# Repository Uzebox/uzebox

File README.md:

The Uzebox is an open source, retro-minimalist game console design. It is based on an AVR 8-bit general purpose microcontroller made by Atmel. The particularity of the system is that it's based on an interrupt driven engine and has no frame buffer. Functions such as video sync generation, tile rendering and music mixing is done realtime in software by a background task so games can easily be developed in C. The design goal was to be as simple as possible yet have good enough sound and graphics while leaving enough resources to implement interesting games. Emphasis was put on making it easy and fun to assemble and program for any hobbyists. The final design contains only two chips: an ATmega644 and an AD725 RGB-to-NTSC converter.

Many commercial versions were available: The Uzebox AVCore by Embedded Engineering llc and the Fuzebox by Adafruit Industries. There was also the Uzebox deluxe kit and the EUzebox, a version with a SCART interface.

Features:
* Interrupt driven: No cycle counting required, sound mixing and video generation are all made in the background
* 5 channels sound engine: The sound subsystem is composed of 3 wavetable channels, 1 noise and 1 PCM channel. Sound is 8-bit mono, mixed at ~15Khz
* 256 simultaneous colors arranged in a 3:3:2 color space (Red:3 bits, Green:3 bits, Blue: 2 bits)
* Resolution: 10+ video modes offering up to 360x224 pixels (tiles-only, tiles & sprites, and bitmap video modes)
* Full screen scrolling in certain video modes
* Sprites: 32+ simultaneous sprites
* Inputs supported: Two SNES compatible joypad inputs (including SNES mouse)
* MIDI IN: With a music sequencer, allows the creation of music directly on the console
* SD/MicroSD and FAT16/32 support
* 'Uzenet' extension for ESP8266 wifi and 128KB SPI RAM
* PS/2 keyboard interface
* Bootloader5 allows you to flash games from a standard FAT16/32 formatted SD card
* Cross-platform emulator with GDB support to ease development
* Multiple tools to convert MIDI, sound file and graphics to include files

The sources come complete with fully functional games, demos, content generation tools and even a cross-platform emulator!

**To find out more, please check out the project's sites:**
* [Getting started](https://uzebox.org/wiki/Getting_Started_on_the_Uzebox): How to install the toolchains, IDEs and build the codebase. Then move on to tutorials and the rest of the documentation.  
* [Main website](https://uzebox.org): The main hub with news, links, downloads and more.
* [Wiki](https://uzebox.org/wiki): All the project's documentation.
* [Forums](https://uzebox.org/forums): Share your new game and discuss everything Uzebox.

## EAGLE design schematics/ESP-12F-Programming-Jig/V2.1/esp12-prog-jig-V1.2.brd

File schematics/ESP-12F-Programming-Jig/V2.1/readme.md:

# ESP-12E/F Programming Jig V1.2 

A jig to program the ESP-12E/F modules based on Espressif's ESP8266 Wi-fi module. Specficially made for FTDI TTL-232R cables.

### Features
* Dual voltage support for the TTL-232R-3V3 (3.3V I/O) and TTL-232R-5V (5V I/O) cables
* Can use pogo pins or headers as mating options
* Programming switches
* Most discretes parts can be ommited if only 3.3V is to be supported

### Notes
* See the the [Uzebox WIKI](https://uzebox.org/wiki/ESP8266_Manual_Upgrade) on the software and procedure required to upgrade the ESP8266 firmware.
* A 3D printed enclosure is available [here](https://github.com/Uzebox/uzebox/tree/master/cad/Enclosures/ESP-12F-Programming-Jig/V1.2).
* Schematic and PCB design files are provided in EAGLE format (.sch, .brd)
* The provided Gerber files can simply be zipped toghether and directly uploaded to PCB manufacturer such as [JLCPCB](https://jlcpcb.com/) and [PCBWay](https://www.pcbway.com/).

### Revisions 
#### V1.2 - Feb-2023
* Replaced tactile switches with through hole versions
* Added color legend on how to connect the FTDI cable correctly

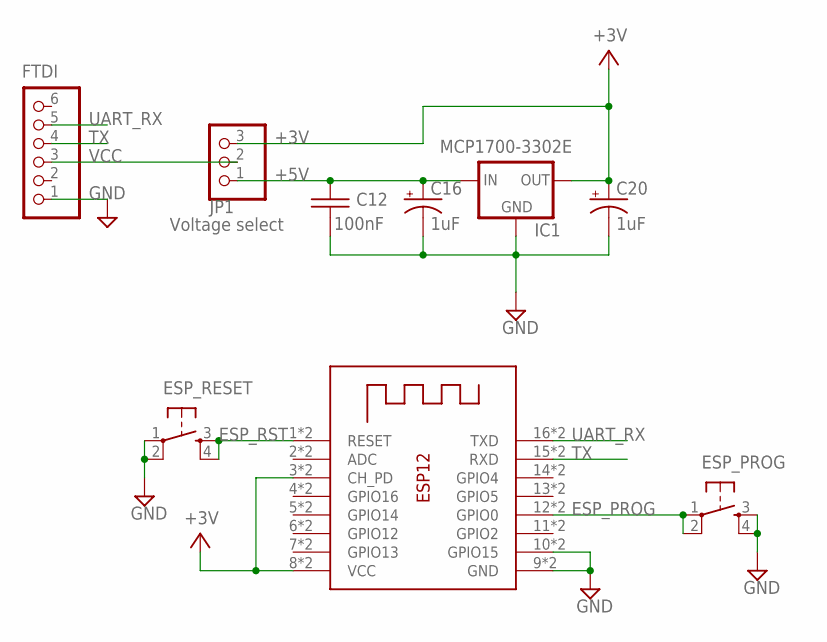
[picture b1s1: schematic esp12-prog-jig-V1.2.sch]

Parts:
C12: 100nF; UZEBOX_CAP_C025
C16, C20: 1uF; UZEBOX_CAP_E5X6
ESP_PROG: UZEBOX_TACTILE_SWITCHPTH; TACTILE-PTH
ESP_RESET: UZEBOX_TACTILE_SWITCHPTH; TACTILE-PTH
FTDI: PINHD-1X6/90; 1X06/90
IC1: MCP1700-3302E; ADAFRUIT_TO92-INLINE
JP1: Voltage select; 1X03
X1: ESP8266-12F; UZEBOX_ESP-12_TH

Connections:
+3V: C20.+, IC1.3 (OUT), JP1.3, X1.3 (CH_PD), X1.8 (VCC), X1.P$3 (CH_PD), X1.P$8 (VCC)
+5V: C12.1, C16.+, IC1.2 (IN), JP1.1
ESP_PROG: ESP_PROG.1, ESP_PROG.2, X1.12 (GPIO0), X1.P$12 (GPIO0)
ESP_RST: ESP_RESET.3, ESP_RESET.4, X1.1 (RESET), X1.P$1 (RESET)
GND: C12.2, C16.-, C20.-, ESP_PROG.3, ESP_PROG.4, ESP_RESET.1, ESP_RESET.2, FTDI.1, IC1.1 (GND), X1.9 (GND), X1.10 (GPIO15), X1.P$9 (GND), X1.P$10 (GPIO15)
TX: FTDI.4, X1.15 (RXD), X1.P$15 (RXD)
UART_RX: FTDI.5, X1.16 (TXD), X1.P$16 (TXD)
VCC: FTDI.3, JP1.2

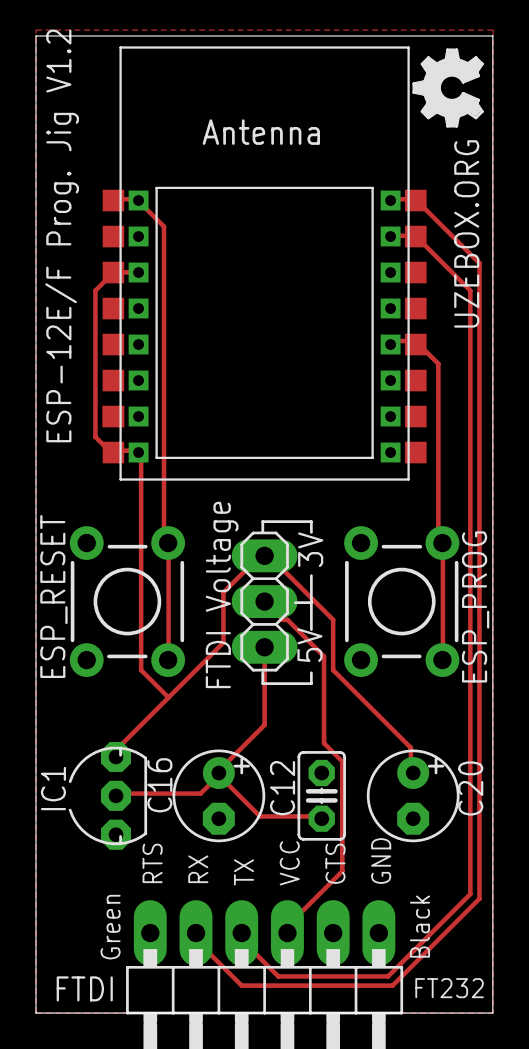
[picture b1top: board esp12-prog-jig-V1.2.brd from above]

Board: 2 copper layers, 25.4 x 54.3 mm, 10 parts (0 on the bottom side), 8 nets.

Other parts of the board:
U$1: OSHW_FILLX150_NOTEXT

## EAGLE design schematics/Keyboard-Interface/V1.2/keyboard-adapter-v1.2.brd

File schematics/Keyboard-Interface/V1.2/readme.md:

# Uzebox Keyboard Interface V1.2 

The keyboard interface allows the Uzebox to communicate with a standard PS/2 keyboard.

See https://uzebox.org/wiki/Uzebox_Keyboard_Interface for more details on the implementation of the interface and the assembly guide.
### Features
* Based on the Atmel ATtiny85/45/25 8-pin DIP
* PS/2 Interface to keyboard 
* Communicates with the Uzebox via a controller port
* Supports bi-directionnal communication
* ISP port to allow reprogramming of the firmware
* Implements the Uzebus protocol

### Notes
* keyboard-adapter-firmware-v2.hex is the latest firmware to be flashed on the ATtiny85. The firmware is built by the [KeyboardFirmware project](/demos/KeyboardFirmware).
* Schematic and PCB design files are provided in EAGLE format (.sch, .brd)
* The provided Gerber files can simply be zipped toghether and directly uploaded to PCB manufacturer such as [JLCPCB](https://jlcpcb.com/) and [PCBWay](https://www.pcbway.com/).

### Revisions 
#### V1.2 - Feb-2023
* Corrected layout issue: Ajusted PCB layout so the ISP progammer's 6 pins header could fit.
* Added pullups on the PS/2 lines since the internal AVR pullups would not work when the tiny85 wanted to send commands to the keyboard.
* Added series resistors on the SNES lines to avoid interfering with ISP programming. Added for development and firmware updates.
* Revamped the PCB design and labeled all components
* Support sending host commands to the keyboard. Implemented to support keyboard that requires the host to send any command right after a reset/BAT. Otherwise the keyboard re-enters BAT (self-test) endlessly sending 0xAA on the bus. This allows the support of PS/2 Perixx keyboards.

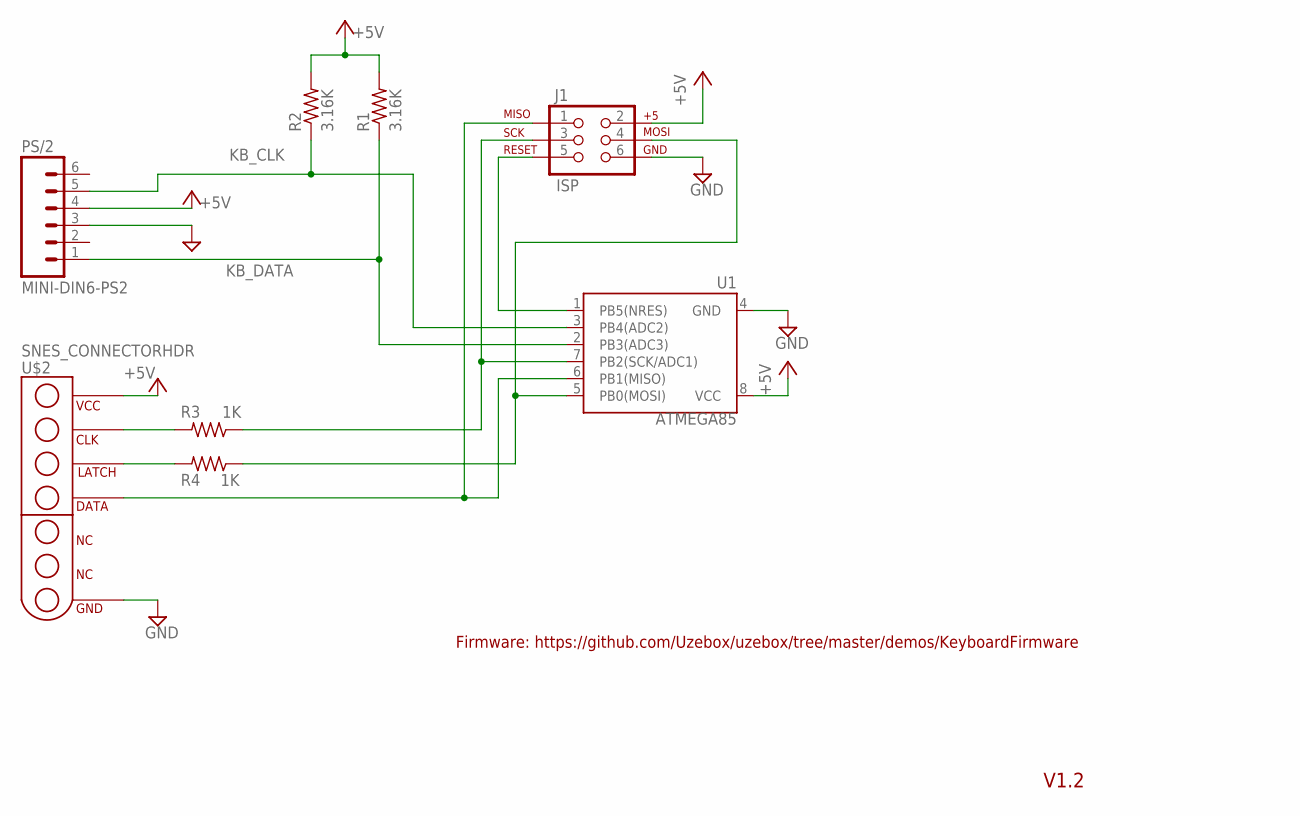
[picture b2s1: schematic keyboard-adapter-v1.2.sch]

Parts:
ATMEGA85: U1; DIP762W53P254L927H508Q8B
J1: ISP; 2X3
PS/2: MINI-DIN6-PS2; MINI-DIN6
R1, R2: 3.16K; 0207/10
R3, R4: 1K; 0207/10
U$2: SNES_CONNECTORHDR; SNES_CONN-HDR5

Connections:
+5V: ATMEGA85.8 (VCC), J1.2, PS/2.4, R1.2, R2.2, U$2.P$5 (VCC)
GND: ATMEGA85.4 (GND), J1.6, PS/2.3, U$2.P$1 (GND)
KB_CLK: ATMEGA85.3 (PB4(ADC2)), PS/2.5, R2.1
KB_DATA: ATMEGA85.2 (PB3(ADC3)), PS/2.1, R1.1
MISO: ATMEGA85.6 (PB1(MISO)), J1.1, U$2.P$2 (DATA)
MOSI: ATMEGA85.5 (PB0(MOSI)), J1.4, R4.1
RESET: ATMEGA85.1 (PB5(NRES)), J1.5
SCK: ATMEGA85.7 (PB2(SCK/ADC1)), J1.3, R3.1
S_CLK: R3.2, U$2.P$4 (CLK)
S_LATCH: R4.2, U$2.P$3 (LATCH)

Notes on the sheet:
V1.2
Firmware: https://github.com/Uzebox/uzebox/tree/master/demos/KeyboardFirmware

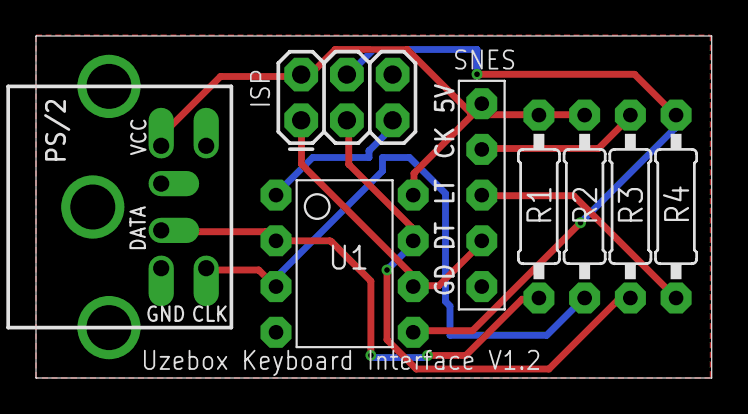
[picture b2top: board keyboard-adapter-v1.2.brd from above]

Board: 2 copper layers, 37.5 x 19.0 mm, 9 parts (1 on the bottom side), 10 nets.

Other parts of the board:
U$1: OSHW_FILLX150_NOTEXT

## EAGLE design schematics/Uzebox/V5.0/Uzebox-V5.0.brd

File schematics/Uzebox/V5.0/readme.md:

### Schematic and PCB design files for the Uzebox reference design V5.0

The Uzebox is a retro-minimalist 8-bit video game console based on only 2 chips.
### Features
* Atmel ATMega644/A/P/PA overclocked at 28Mhz
* NTSC video generation with the AD725 RGB-to-NTSC converter chip
* Composite and S-Video outputs
* SD card interface
* ESP-12E/F Wi-fi module that can be soldered via castlated pads or in a through hole fashion.
* SPI RAM support
* Two SNES controller sockets
* Reset and soft power buttons
* ISP Port
* Extension header

### Revisions
* PCB rev.1.3.3
* Replaced the MIDI interface with Uzenet interface
* Added second ISP footprint for 90 deg connectors
* New footprint for SD card connector (see BOM)

### Assembly guide
* The assembly guide is part of the project [here](Uzebox-V5.0-assembly-guide.md).

### Notes
* Schematic and PCB design files are provided in EAGLE format (.sch, .brd)
* The provided Gerber files can simply be zipped toghether and directly uploaded to PCB manufacturer such as [JLCPCB](https://jlcpcb.com/) and [PCBWay](https://www.pcbway.com/).
* A Digikey shopping list is available to quickly order all parts. The list is continuously maintained as parts goes out of stock. https://www.digikey.ca/en/mylists/list/QP8GNGSW4R

### Links
* [Uzebox website](https://uzebox.org/index.php)
* [Uzebox Forums](https://uzebox.org/forums/)
* [uzebox WIKI](https://uzebox.org/wiki/Main_Page)

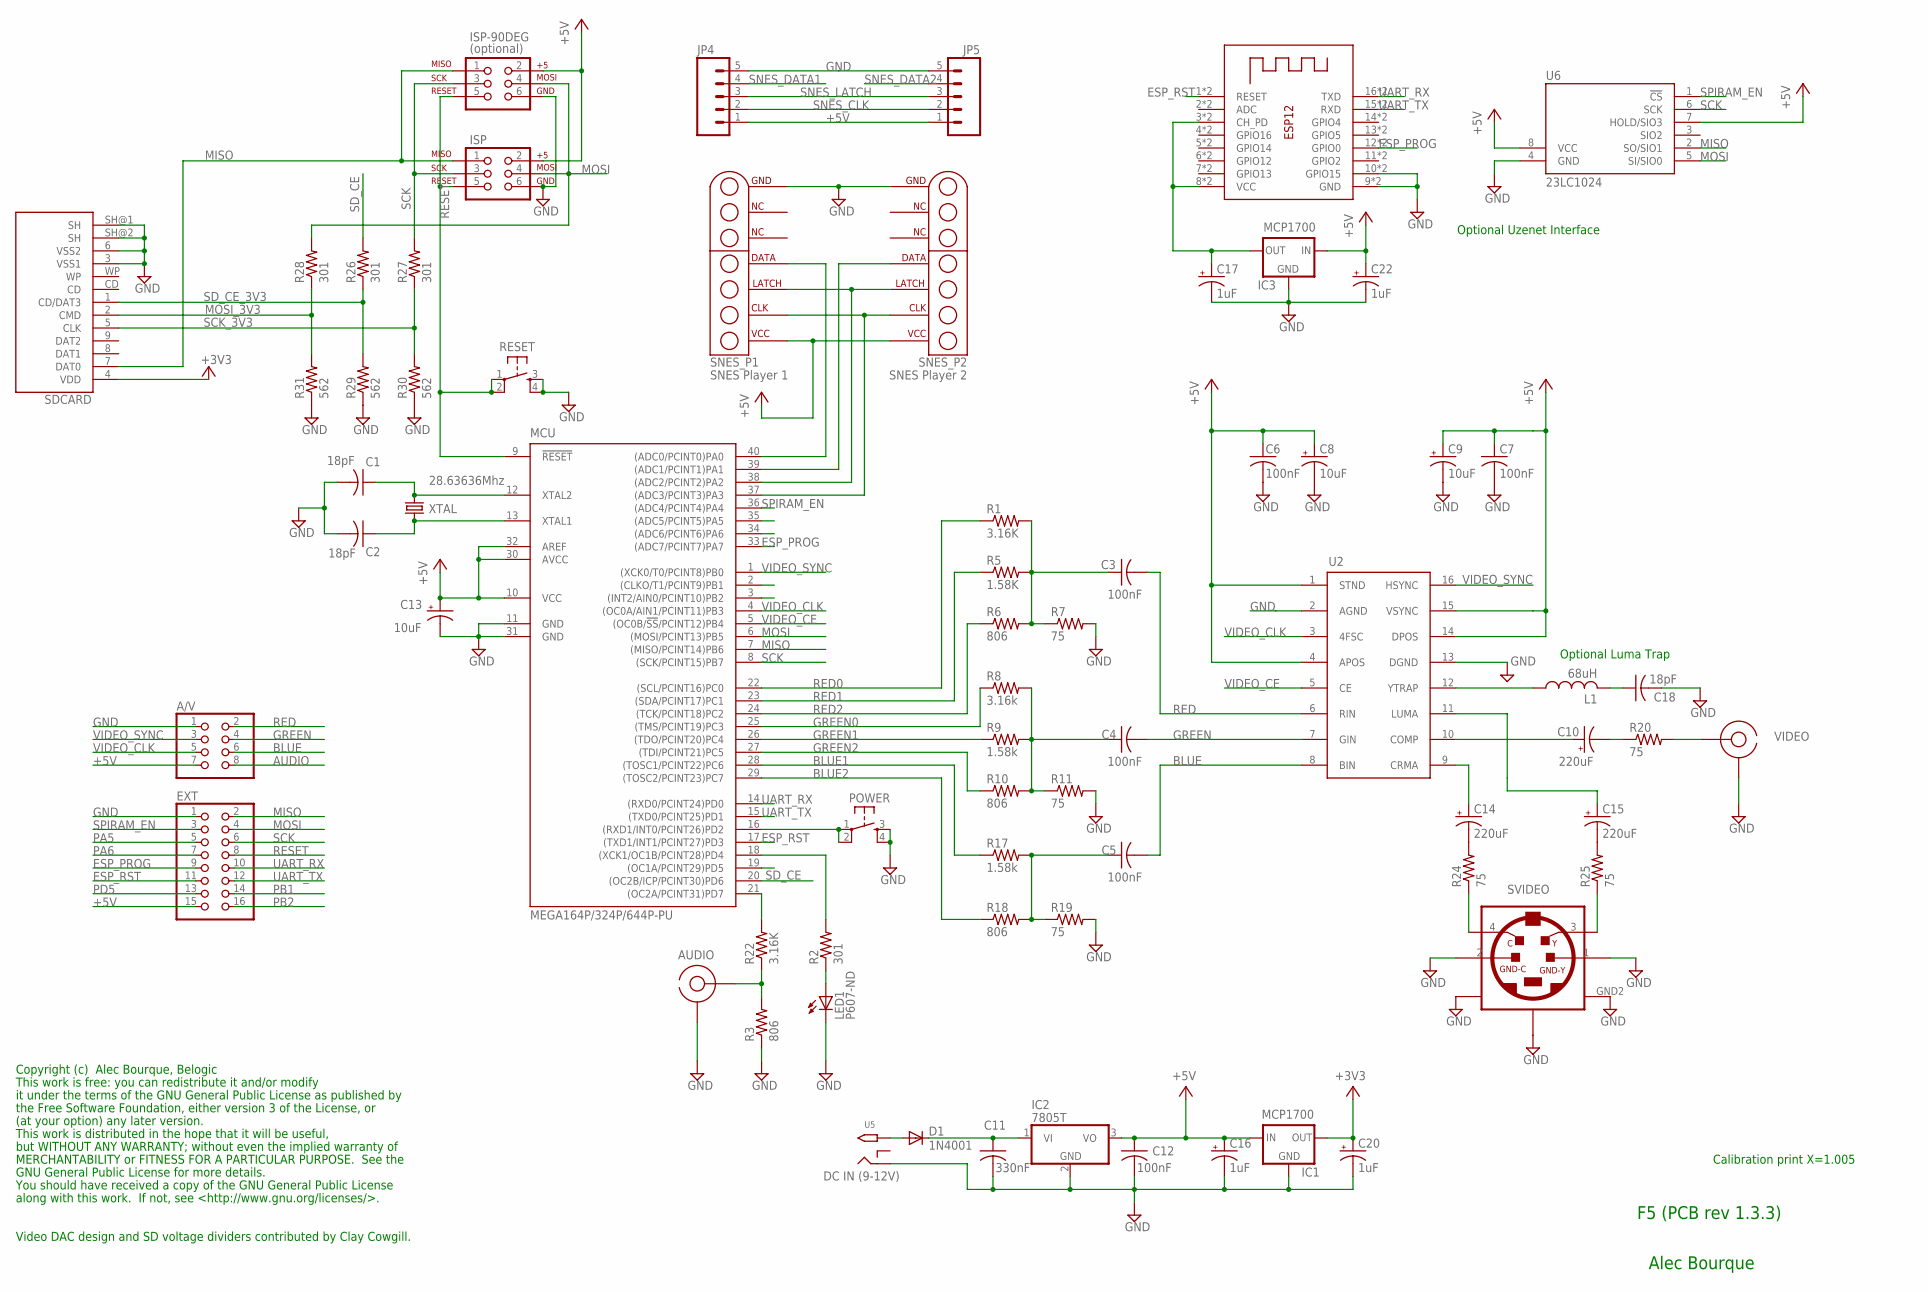
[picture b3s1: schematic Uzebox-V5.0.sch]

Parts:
A/V: PINHD-2X4; 2X04
AD725: AD725; SO16W
AUDIO: RCA
C1, C2, C18: 18pF; C025-025X050
C3, C4, C5, C6, C7, C12: 100nF; C025-025X050
C8, C9, C13: 10uF; E2,5-6
C10, C14, C15: 220uF; E2,5-6
C11: 330nF; C025-025X050
C16, C20: 1uF; E2,5-6
C17, C22: 1uF; E2-4
D1: 1N4001; DO41-10
ESP-12: ESP-12; UZEBOX_ESP-12_TH
EXT: PINHD-2X8; 2X08
IC1, IC3: MCP1700; TO92-INLINE
IC2: 7805T; TO220H
ISP: AVR_SPI_PRG_6PTH; 2X3
ISP-90DEG: (optional); 2X3
JP4, JP5: M05PTH; 1X05
L1: 68uH; 6000-XXXX-RC
LED1: P607-ND; LED3MM
MCU: MEGA164P/324P/644P-PU; DIL40
POWER: USER; TACTILE-PTH
R1, R22: 3.16K; 0207/10
R2, R26, R27, R28: 301; 0207/10
R3, R6, R10, R18: 806; 0207/10
R5: 1.58K; 0207/10
R7, R11, R19, R20, R24, R25: 75; 0207/10
R8: 3.16k; 0207/10
R9, R17: 1.58k; 0207/10
R29, R30, R31: 562; 0207/10
RESET: RESET; TACTILE-PTH
SDCARD: SD_CARD_SOCKET4UCON; SDCARD_4UCONN
SNES_P1: SNES Player 1; SNES_CONNECTOR
SNES_P2: SNES Player 2; SNES_CONNECTOR
SVIDEO: S-VIDEO OUT; MINIDIN4
U5: DC IN; PJ-102A
U6: 23LC1024; DIL08
VIDEO: RCA
XTAL: 28.63636Mhz; HC49/S

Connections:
3V3_ESP: C17.+, ESP-12.3 (CH_PD), ESP-12.8 (VCC), ESP-12.P$3 (CH_PD), ESP-12.P$8 (VCC), IC3.3 (OUT)
+3V3: C20.+, IC1.3 (OUT), SDCARD.4 (VDD)
+5V: A/V.7, AD725.1 (STND), AD725.4 (APOS), AD725.14 (DPOS), AD725.15 (VSYNC), C6.1, C7.1, C8.+, C9.+, C12.1, C13.+, C16.+, C22.+, EXT.15, IC1.2 (IN), IC2.3 (VO), IC3.2 (IN), ISP.2, ISP-90DEG.2, JP4.1, JP5.1, MCU.10 (VCC), MCU.30 (AVCC), MCU.32 (AREF), SNES_P1.P$8 (VCC), SNES_P2.P$8 (VCC), U6.7 (HOLD/SIO3), U6.8 (VCC)
AUDIO: A/V.8, AUDIO.SIG, R3.2, R22.1
BLUE: A/V.6, AD725.8 (BIN), C5.2
BLUE1: MCU.28 ((TOSC1/PCINT22)PC6), R17.1
BLUE2: MCU.29 ((TOSC2/PCINT23)PC7), R18.1
ESP_PROG: ESP-12.12 (GPIO0), ESP-12.P$12 (GPIO0), EXT.9, MCU.33 ((ADC7/PCINT7)PA7)
ESP_RST: ESP-12.1 (RESET), ESP-12.P$1 (RESET), EXT.11, MCU.17 ((TXD1/INT1/PCINT27)PD3)
GND: A/V.1, AD725.2 (AGND), AD725.13 (DGND), AUDIO.GND, C1.2, C2.2, C6.2, C7.2, C8.-, C9.-, C11.2, C12.2, C13.-, C16.-, C17.-, C18.2, C20.-, C22.-, ESP-12.9 (GND), ESP-12.10 (GPIO15), ESP-12.P$9 (GND), ESP-12.P$10 (GPIO15), EXT.1, IC1.1 (GND), IC2.2 (GND), IC3.1 (GND), ISP.6, ISP-90DEG.6, JP4.5, JP5.5, LED1.K (C), MCU.11 (GND), MCU.31 (GND), POWER.3, POWER.4, R3.1, R7.2, R11.2, R19.2, R29.1, R30.1, R31.1, RESET.3, RESET.4, SDCARD.3 (VSS1), SDCARD.6 (VSS2), SDCARD.SH@1 (SH), SDCARD.SH@2 (SH), SNES_P1.P$14 (GND), SNES_P2.P$14 (GND), SVIDEO.1 (GND-Y), SVIDEO.2 (GND-C), SVIDEO.GND1, SVIDEO.GND2, SVIDEO.GND3, U5.RING, U6.4 (GND), VIDEO.GND
GREEN: A/V.4, AD725.7 (GIN), C4.2
GREEN0: MCU.25 ((TMS/PCINT19)PC3), R8.1
GREEN1: MCU.26 ((TDO/PCINT20)PC4), R9.1
GREEN2: MCU.27 ((TDI/PCINT21)PC5), R10.1
MISO: EXT.2, ISP.1, ISP-90DEG.1, MCU.7 ((MISO/PCINT14)PB6), SDCARD.7 (DAT0), U6.2 (SO/SIO1)
MOSI: EXT.4, ISP.4, ISP-90DEG.4, MCU.6 ((MOSI/PCINT13)PB5), R28.2, U6.5 (SI/SIO0)
MOSI_3V3: R28.1, R31.2, SDCARD.2 (CMD)
unnamed: AD725.12 (YTRAP), L1.1
unnamed: C18.1, L1.2
unnamed: C5.1, R17.2, R18.2, R19.1
unnamed: C4.1, R8.2, R9.2, R10.2, R11.1
unnamed: C3.1, R1.2, R5.2, R6.2, R7.1
unnamed: C10.-, R20.1
unnamed: AD725.10 (COMP), C10.+
unnamed: R20.2, VIDEO.SIG
unnamed: C1.1, MCU.12 (XTAL2), XTAL.2
unnamed: D1.A, U5.TIP
unnamed: C14.-, R24.2
unnamed: C2.1, MCU.13 (XTAL1), XTAL.1
unnamed: MCU.21 ((OC2A/PCINT31)PD7), R22.2
unnamed: C11.1, D1.C, IC2.1 (VI)
unnamed: MCU.18 ((XCK1/OC1B/PCINT28)PD4), R2.2
unnamed: LED1.A, R2.1
unnamed: C15.-, R25.2
unnamed: AD725.11 (LUMA), C15.+
unnamed: AD725.9 (CRMA), C14.+
unnamed: R24.1, SVIDEO.4 (C)
unnamed: R25.1, SVIDEO.3 (Y)
PA5: EXT.5, MCU.35 ((ADC5/PCINT5)PA5)
PA6: EXT.7, MCU.34 ((ADC6/PCINT6)PA6)
PB1: EXT.14, MCU.2 ((CLKO/T1/PCINT9)PB1)
PB2: EXT.16, MCU.3 ((INT2/AIN0/PCINT10)PB2)
PD5: EXT.13, MCU.19 ((OC1A/PCINT29)PD5)
POWER_SW: MCU.16 ((RXD1/INT0/PCINT26)PD2), POWER.1, POWER.2
RED: A/V.2, AD725.6 (RIN), C3.2
RED0: MCU.22 ((SCL/PCINT16)PC0), R1.1
RED1: MCU.23 ((SDA/PCINT17)PC1), R5.1
RED2: MCU.24 ((TCK/PCINT18)PC2), R6.1
RESET: EXT.8, ISP.5, ISP-90DEG.5, MCU.9 (!RESET), RESET.1, RESET.2
SCK: EXT.6, ISP.3, ISP-90DEG.3, MCU.8 ((SCK/PCINT15)PB7), R27.2, U6.6 (SCK)
SCK_3V3: R27.1, R30.2, SDCARD.5 (CLK)
SD_CE: MCU.20 ((OC2B/ICP/PCINT30)PD6), R26.2
SD_CE_3V3: R26.1, R29.2, SDCARD.1 (CD/DAT3)
SNES_CLK: JP4.2, JP5.2, MCU.37 ((ADC3/PCINT3)PA3), SNES_P1.P$9 (CLK), SNES_P2.P$9 (CLK)
SNES_DATA1: JP4.4, MCU.40 ((ADC0/PCINT0)PA0), SNES_P1.P$11 (DATA)
SNES_DATA2: JP5.4, MCU.39 ((ADC1/PCINT1)PA1), SNES_P2.P$11 (DATA)
SNES_LATCH: JP4.3, JP5.3, MCU.38 ((ADC2/PCINT2)PA2), SNES_P1.P$10 (LATCH), SNES_P2.P$10 (LATCH)
SPIRAM_EN: EXT.3, MCU.36 ((ADC4/PCINT4)PA4), U6.1 (!CS)
UART_RX: ESP-12.16 (TXD), ESP-12.P$16 (TXD), EXT.10, MCU.14 ((RXD0/PCINT24)PD0)
UART_TX: ESP-12.15 (RXD), ESP-12.P$15 (RXD), EXT.12, MCU.15 ((TXD0/PCINT25)PD1)
VIDEO_CE: AD725.5 (CE), MCU.5 ((OC0B/!SS!/PCINT12)PB4)
VIDEO_CLK: A/V.5, AD725.3 (4FSC), MCU.4 ((OC0A/AIN1/PCINT11)PB3)
VIDEO_SYNC: A/V.3, AD725.16 (HSYNC), MCU.1 ((XCK0/T0/PCINT8)PB0)

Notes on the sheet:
Optional Luma Trap
Alec Bourque
Copyright (c) Alec Bourque, Belogic
This work is free: you can redistribute it and/or modify
it under the terms of the GNU General Public License as published by
the Free Software Foundation, either version 3 of the License, or
(at your option) any later version.
This work is distributed in the hope that it will be useful,
but WITHOUT ANY WARRANTY; without even the implied warranty of
MERCHANTABILITY or FITNESS FOR A PARTICULAR PURPOSE. See the
GNU General Public License for more details.
You should have received a copy of the GNU General Public License
along with this work. If not, see <http://www.gnu.org/licenses/>.
Calibration print X=1.005
Video DAC design and SD voltage dividers contributed by Clay Cowgill.
F5 (PCB rev 1.3.3)
Optional Uzenet Interface

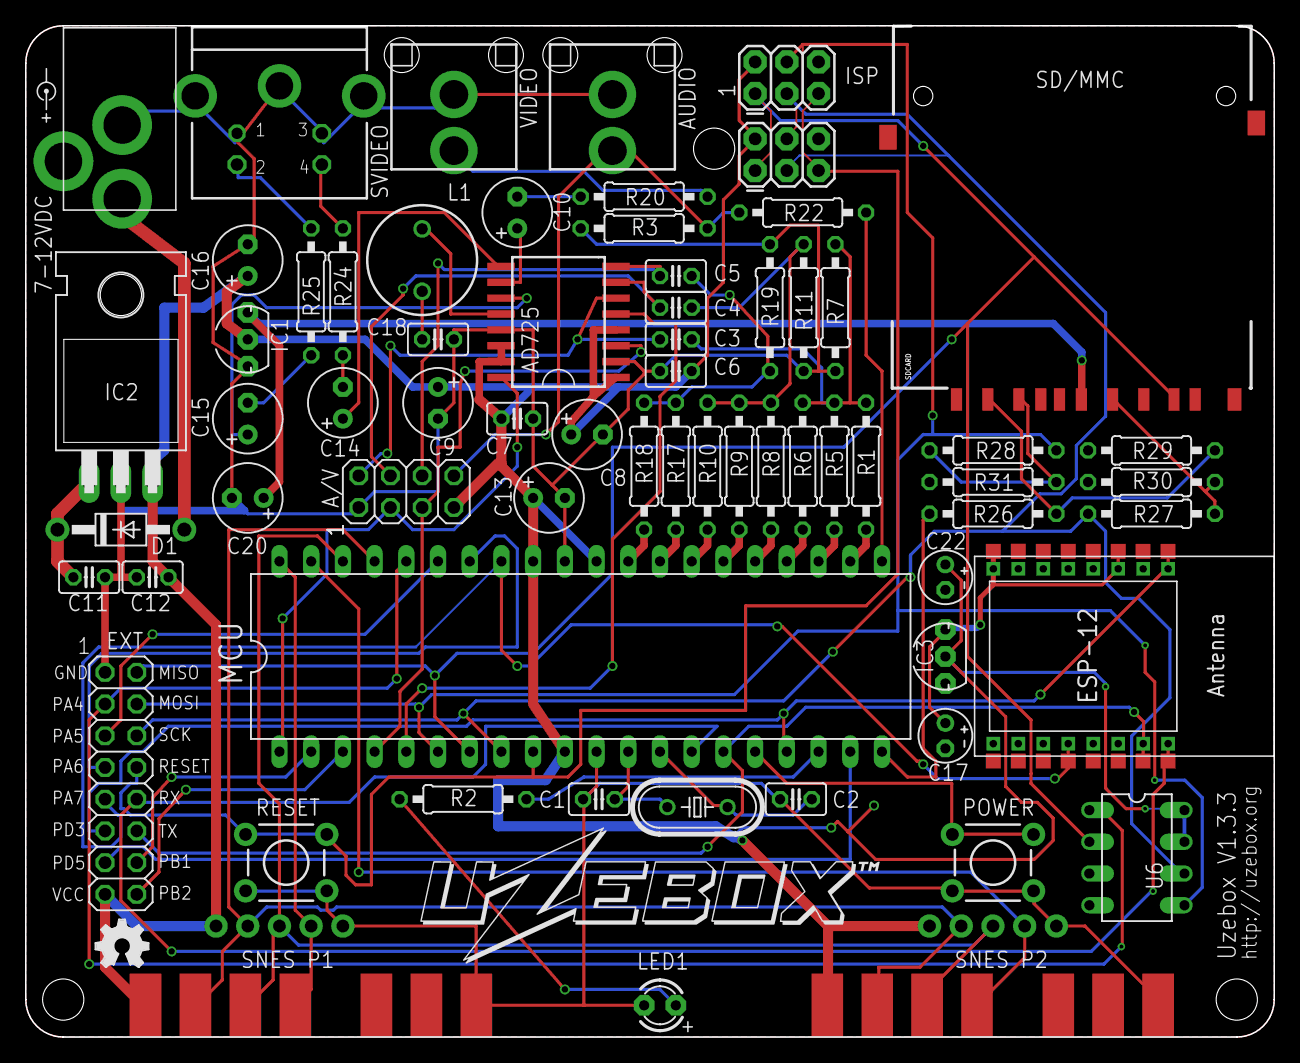
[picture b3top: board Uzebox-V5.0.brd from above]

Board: 2 copper layers, 100.0 x 81.0 mm, 79 parts (0 on the bottom side), 63 nets.

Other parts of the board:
U$1: OSHW_FILLX150_NOTEXT
U$2, U$3, U$4: STAND-OFF
U$6: LOGO
U$7: POWER
U$8, U$9, U$10, U$11: BUMPON

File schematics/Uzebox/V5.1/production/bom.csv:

Designator,Footprint,Quantity,Value,LCSC Part #
A/V,2X04,1,PINHD-2X4,
AD725,SO16W,1,AD725,
"AUDIO, VIDEO",RCA,2,RCA,
"C1, C18, C2",C025-025X050,3,18pF,
"C10, C14, C15","E2,5-6",3,220uF,
C11,C025-025X050,1,330nF,
"C12, C3, C4, C5, C6, C7",C025-025X050,6,100nF,
"C13, C8, C9","E2,5-6",3,10uF,
"C16, C20","E2,5-6",2,1uF,
"C17, C22",E2-4,2,1uF,
D1,DO41-10,1,1N4001,
D2,DO35-7,1,BAT85,
ESP-12,UZEBOX_ESP-12_TH,1,ESP-12,
EXT,2X08,1,PINHD-2X8,
"IC1, IC3",TO92-INLINE,2,MCP1700,
IC2,TO220H,1,78T05,
ISP,2X3,1,AVR_SPI_PRG_6PTH,
ISP-90DEG1,2X3,1,(optional),
J1,PinHeader_1x05_P2.54mm_Vertical,1,P1,
J2,PinHeader_1x05_P2.54mm_Vertical,1,P2,
L1,6000-XXXX-RC,1,68uH,
LED,LED3MM,1,P607-ND,
MCU,DIL40,1,ATMEGA644P-PU,
POWER,TACTILE-PTH,1,USER,
"R1, R12, R13, R22, R4, R8",0207_10,6,3.16K,
"R10, R18, R3, R6",0207_10,4,806,
"R11, R19, R20, R24, R25, R7",0207_10,6,75,
"R17, R5, R9",0207_10,3,1.58k,
"R2, R27, R28",0207_10,3,301,
"R30, R31",0207_10,2,562,
RESET,TACTILE-PTH,1,RESET,
SDCARD,SDCARD_4UCONN,1,SD_CARD_SOCKET4UCON,
SNES_P1,SNES_CONNECTOR,1,SNES Player 1,
SNES_P2,SNES_CONNECTOR,1,SNES Player 2,
SVIDEO,MINIDIN4,1,S-VIDEO OUT,
U5,PJ-102A,1,DC IN,
U6,DIL08,1,23LC1024,
XTAL0,HC49_S,1,28.63636Mhz,

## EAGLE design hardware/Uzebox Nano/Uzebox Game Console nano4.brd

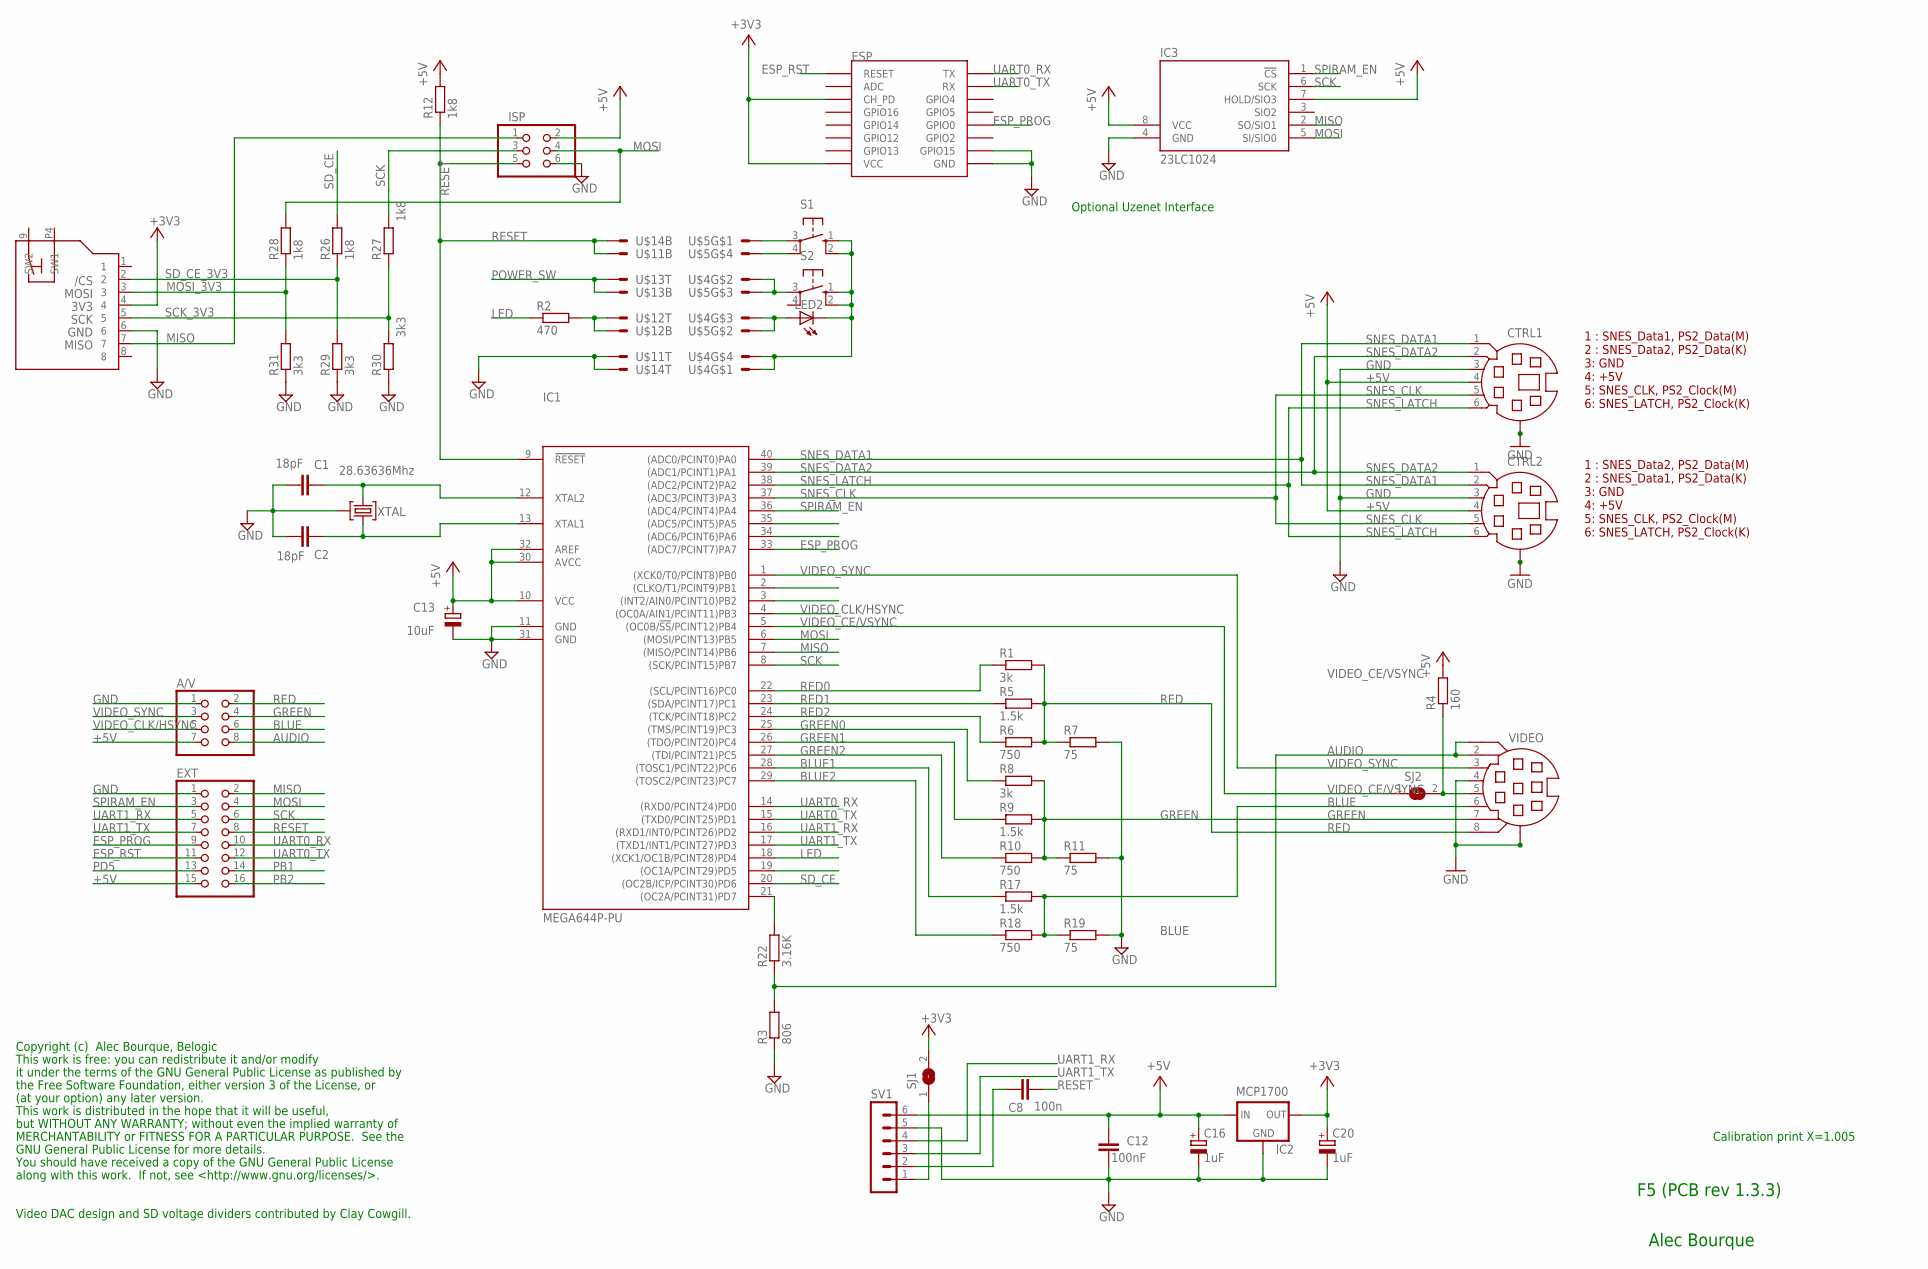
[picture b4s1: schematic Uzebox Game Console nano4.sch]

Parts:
A/V: PINHD-2X4; 2X04
C1, C2: 18pF; C025-025X050
C8: 100n; C025-025X050
C12: 100nF; C025-025X050
C13: 10uF; E2,5-6
C16, C20: 1uF; E2,5-6
CTRL1, CTRL2: MINI-DIN-6
ESP: ESP12SMD; ESP12-SMD
EXT: PINHD-2X8; 2X08
IC1: MEGA644P-PU; DIL40
IC2: MCP1700; TO92-INLINE
IC3: 23LC1024; DIL08
ISP: PINHD-2X3; 2X03
J1: MICROSD-SWITCH; MICROSD-ATOM
LED2: LED3MM
R1, R8: 3k; 0207/10
R2: 470; 0207/10
R3: 806; 0207/10
R4: 160; 0207/10
R5, R9, R17: 1.5k; 0207/10
R6, R10, R18: 750; 0207/10
R7, R11, R19: 75; 0207/10
R12, R26, R27, R28: 1k8; 0207/10
R22: 3.16K; 0207/10
R29, R30, R31: 3k3; 0207/10
S1, S2: 10-XX; B3F-10XX
SJ1, SJ2: SJ
SV1: MA06-1
U$1: PCB_CONNECTOR_4X2; PCB_CONNECTOR_2X4POL
U$4, U$5: PCB_CONNECTOR_1X4POL
VIDEO: MINI-DIN-8
XTAL: 28.63636Mhz; HC49TL-H

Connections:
+3V3: C20.+, ESP.CH_PD, ESP.VCC, IC2.3 (OUT), J1.4, SJ1.2
+5V: A/V.7, C12.1, C13.+, C16.+, CTRL1.4, CTRL2.4, EXT.15, IC1.10 (VCC), IC1.30 (AVCC), IC1.32 (AREF), IC2.2 (IN), IC3.7 (HOLD/SIO3), IC3.8 (VCC), ISP.2, R4.2, R12.2, SV1.6
AUDIO: A/V.8, R3.2, R22.1, VIDEO.1, VIDEO.2
BLUE: A/V.6, R17.2, R18.2, R19.1, VIDEO.6
BLUE1: IC1.28 ((TOSC1/PCINT22)PC6), R17.1
BLUE2: IC1.29 ((TOSC2/PCINT23)PC7), R18.1
ESP_PROG: ESP.GPIO0, EXT.9, IC1.33 ((ADC7/PCINT7)PA7)
ESP_RST: ESP.RESET, EXT.11, IC1.34 ((ADC6/PCINT6)PA6)
GND: A/V.1, C1.2, C2.2, C12.2, C13.-, C16.-, C20.-, CTRL1.3, CTRL1.G, CTRL1.G1, CTRL1.G2, CTRL2.3, CTRL2.G, CTRL2.G1, CTRL2.G2, ESP.GND, ESP.GPIO15, EXT.1, IC1.11 (GND), IC1.31 (GND), IC2.1 (GND), IC3.4 (GND), ISP.6, J1.6, R3.1, R7.2, R11.2, R19.2, R29.1, R30.1, R31.1, SV1.5, U$1.1T, U$1.4T, VIDEO.4, VIDEO.G (G1), VIDEO.G1 (G2), VIDEO.G2 (G3), XTAL.3
GREEN: A/V.4, R8.2, R9.2, R10.2, R11.1, VIDEO.7
GREEN0: IC1.25 ((TMS/PCINT19)PC3), R8.1
GREEN1: IC1.26 ((TDO/PCINT20)PC4), R9.1
GREEN2: IC1.27 ((TDI/PCINT21)PC5), R10.1
LED: IC1.18 ((XCK1/OC1B/PCINT28)PD4), R2.1
MISO: EXT.2, IC1.7 ((MISO/PCINT14)PB6), IC3.2 (SO/SIO1), ISP.1, J1.7
MOSI: EXT.4, IC1.6 ((MOSI/PCINT13)PB5), IC3.5 (SI/SIO0), ISP.4, R28.2
MOSI_3V3: J1.3, R28.1, R31.2
unnamed: R4.1, SJ2.2, VIDEO.5
unnamed: C8.2, SV1.2
unnamed: C1.1, IC1.12 (XTAL2), XTAL.2
unnamed: C2.1, IC1.13 (XTAL1), XTAL.1
unnamed: IC1.21 ((OC2A/PCINT31)PD7), R22.2
unnamed: R2.2, U$1.2B, U$1.2T
unnamed: LED2.K (C), S1.1 (S), S1.2 (S1), S2.1 (S), S2.2 (S1), U$4.1T, U$4.4T
unnamed: SJ1.1, SV1.1
unnamed: S1.3, U$5.1T
unnamed: S2.3, U$4.2T, U$5.3T
unnamed: S1.4 (P1), U$5.4T
unnamed: LED2.A, U$4.3T, U$5.2T
PB1: EXT.14, IC1.2 ((CLKO/T1/PCINT9)PB1)
PB2: EXT.16, IC1.3 ((INT2/AIN0/PCINT10)PB2)
PD5: EXT.13, IC1.19 ((OC1A/PCINT29)PD5)
POWER_SW: IC1.35 ((ADC5/PCINT5)PA5), U$1.3B, U$1.3T
RED: A/V.2, R1.2, R5.2, R6.2, R7.1, VIDEO.8
RED0: IC1.22 ((SCL/PCINT16)PC0), R1.1
RED1: IC1.23 ((SDA/PCINT17)PC1), R5.1
RED2: IC1.24 ((TCK/PCINT18)PC2), R6.1
RESET: C8.1, EXT.8, IC1.9 (!RESET), ISP.5, R12.1, U$1.1B, U$1.4B
SCK: EXT.6, IC1.8 ((SCK/PCINT15)PB7), IC3.6 (SCK), ISP.3, R27.2
SCK_3V3: J1.5, R27.1, R30.2
SD_CE: IC1.20 ((OC2B/ICP/PCINT30)PD6), R26.2
SD_CE_3V3: J1.2, R26.1, R29.2
SNES_CLK: CTRL1.5, CTRL2.5, IC1.37 ((ADC3/PCINT3)PA3)
SNES_DATA1: CTRL1.1, CTRL2.2, IC1.40 ((ADC0/PCINT0)PA0)
SNES_DATA2: CTRL1.2, CTRL2.1, IC1.39 ((ADC1/PCINT1)PA1)
SNES_LATCH: CTRL1.6, CTRL2.6, IC1.38 ((ADC2/PCINT2)PA2)
SPIRAM_EN: EXT.3, IC1.36 ((ADC4/PCINT4)PA4), IC3.1 (!CS)
UART0_RX: ESP.TXD0 (TX), EXT.10, IC1.14 ((RXD0/PCINT24)PD0)
UART0_TX: ESP.RXD0 (RX), EXT.12, IC1.15 ((TXD0/PCINT25)PD1)
UART1_RX: EXT.5, IC1.16 ((RXD1/INT0/PCINT26)PD2), SV1.4
UART1_TX: EXT.7, IC1.17 ((TXD1/INT1/PCINT27)PD3), SV1.3
VIDEO_CE/VSYNC: IC1.5 ((OC0B/!SS!/PCINT12)PB4), SJ2.1
VIDEO_CLK/HSYNC: A/V.5, IC1.4 ((OC0A/AIN1/PCINT11)PB3)
VIDEO_SYNC: A/V.3, IC1.1 ((XCK0/T0/PCINT8)PB0), VIDEO.3

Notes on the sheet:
Alec Bourque
Copyright (c) Alec Bourque, Belogic
This work is free: you can redistribute it and/or modify
it under the terms of the GNU General Public License as published by
the Free Software Foundation, either version 3 of the License, or
(at your option) any later version.
This work is distributed in the hope that it will be useful,
but WITHOUT ANY WARRANTY; without even the implied warranty of
MERCHANTABILITY or FITNESS FOR A PARTICULAR PURPOSE. See the
GNU General Public License for more details.
You should have received a copy of the GNU General Public License
along with this work. If not, see <http://www.gnu.org/licenses/>.
Calibration print X=1.005
Video DAC design and SD voltage dividers contributed by Clay Cowgill.
F5 (PCB rev 1.3.3)
Optional Uzenet Interface
1 : SNES_Data1, PS2_Data(M) 2 : SNES_Data2, PS2_Data(K) 3: GND 4: +5V 5: SNES_CLK, PS2_Clock(M) 6: SNES_LATCH, PS2_Clock(K)
1 : SNES_Data2, PS2_Data(M) 2 : SNES_Data1, PS2_Data(K) 3: GND 4: +5V 5: SNES_CLK, PS2_Clock(M) 6: SNES_LATCH, PS2_Clock(K)

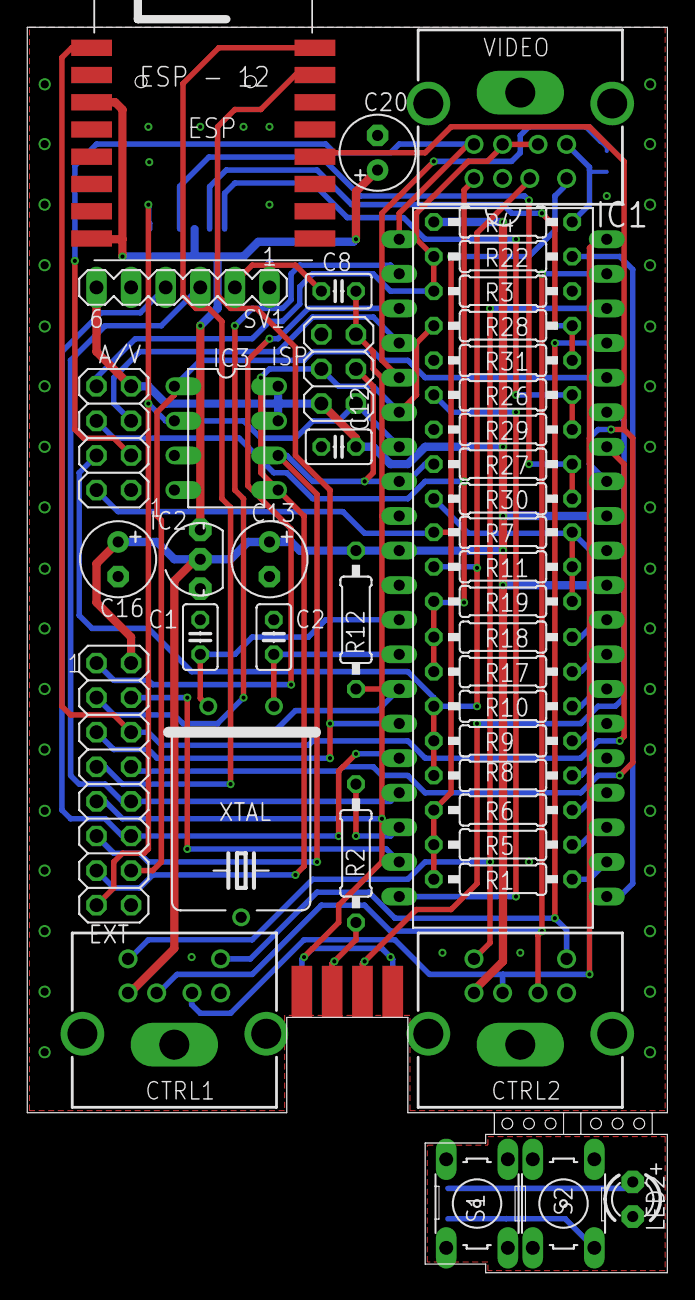
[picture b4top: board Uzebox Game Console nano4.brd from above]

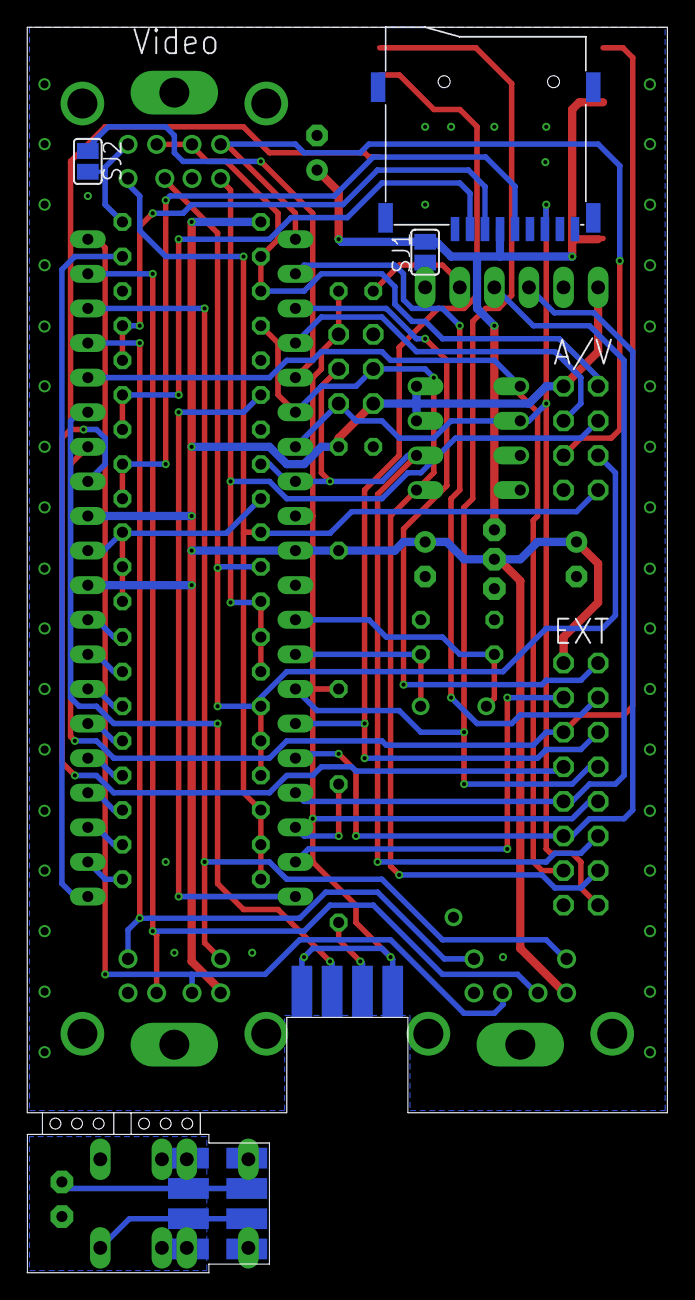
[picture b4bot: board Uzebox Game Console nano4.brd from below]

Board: 2 copper layers, 47.0 x 91.4 mm, 51 parts (5 on the bottom side), 54 nets.

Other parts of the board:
U$6: LOGO

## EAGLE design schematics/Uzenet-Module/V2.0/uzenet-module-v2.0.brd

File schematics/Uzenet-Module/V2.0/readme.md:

The Uzenet module V2.0 allows any Uzebox or compatible equipped with the standard EXT header to connect to a Wi-Fi network. It also includes a SPI RAM module providing an extra 128K to games and applications. Wi-Fi connectivity is accomplished using the common ESP8266 ESP-12E/F module using Espressif's stock firmware. Applications communicates with the ESP-12 module using plain AT commands.

### Notes
* Schematic and PCB design files are provided in EAGLE format 
* The provided Gerber files can simply be zipped toghether and directly uploaded to PCB manufacturer such as [JLCPCB](https://jlcpcb.com/) and [PCBWay](https://www.pcbway.com/).
* It's recommended to upgrade the ESP-12 to the latest version. See the wiki for the [manual update procedure](https://uzebox.org/wiki/ESP8266_Manual_Upgrade). 
* A Digikey shopping list is available to quickly order all parts. The list is continuously maintained as parts goes out of stock. https://www.digikey.ca/en/mylists/list/SRSY6ZW28E

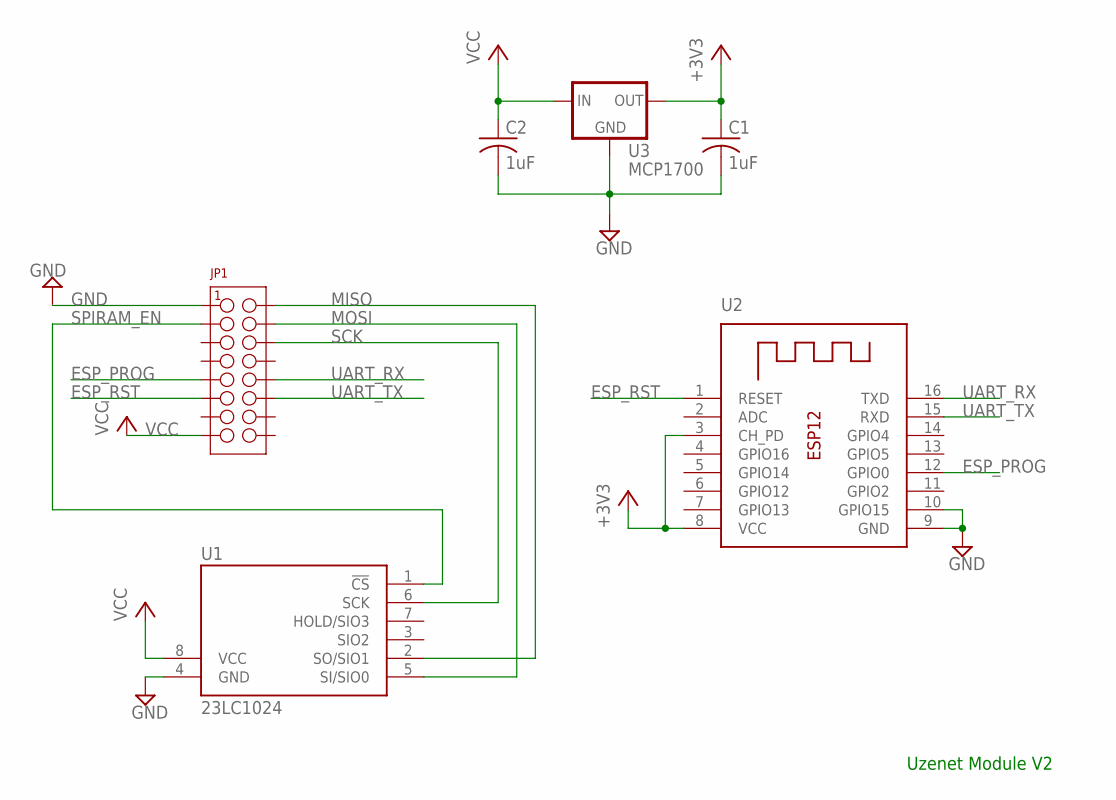
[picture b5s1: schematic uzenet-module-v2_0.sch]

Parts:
C1, C2: 1uF; C025-025X050
JP1: NPPC082KFMS-RC; HEADER_2X8_SMT_BOTTOM_LAYER
U1: 23LC1024; DIL08
U2: ESP-12
U3: MCP1700; TO92-INLINE

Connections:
+3V3: C1.1, U2.3 (CH_PD), U2.8 (VCC), U3.3 (OUT)
ESP_PROG: JP1.P$9, U2.12 (GPIO0)
ESP_RST: JP1.P$11, U2.1 (RESET)
GND: C1.2, C2.2, JP1.P$1, U1.4 (GND), U2.9 (GND), U2.10 (GPIO15), U3.1 (GND)
MISO: JP1.P$2, U1.2 (SO/SIO1)
MOSI: JP1.P$4, U1.5 (SI/SIO0)
SCK: JP1.P$6, U1.6 (SCK)
SPIRAM_EN: JP1.P$3, U1.1 (!CS)
UART_RX: JP1.P$10, U2.16 (TXD)
UART_TX: JP1.P$12, U2.15 (RXD)
VCC: C2.1, JP1.P$15, U1.8 (VCC), U3.2 (IN)

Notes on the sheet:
Uzenet Module V2

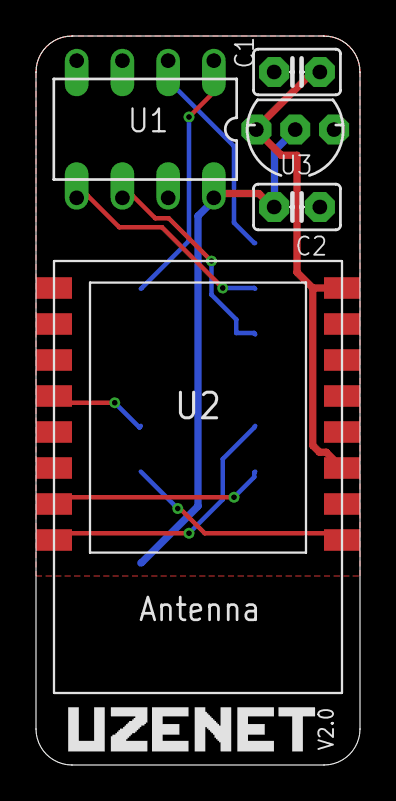
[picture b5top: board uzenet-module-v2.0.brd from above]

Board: 2 copper layers, 18.0 x 40.5 mm, 7 parts (0 on the bottom side), 11 nets.

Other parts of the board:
U$1: UZENETLOGO

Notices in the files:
parts and their libraries:
SparkFun-Connectors: Licensing: CC v3.0 Share-Alike You are welcome to use this library for commercial purposes.
